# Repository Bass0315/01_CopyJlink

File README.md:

# Jflash auto dowmload
#### 介绍
> 该项目是 Windows/Linux 下Jflash的自动烧录脚本。

#### 支持
Linux：
> sudo apt-get install libudev-dev
> sudo apt-get install gcc./
> sudo apt-get install build-essential
> Install libusb (https://blog.csdn.net/p1279030826/article/details/102891704)
> ~$ sudo cp 99-jlink.rules /etc/udev/rules.d 

#### 使用
Linux：
> Program.sh  xxx.bin/hex

Windows:

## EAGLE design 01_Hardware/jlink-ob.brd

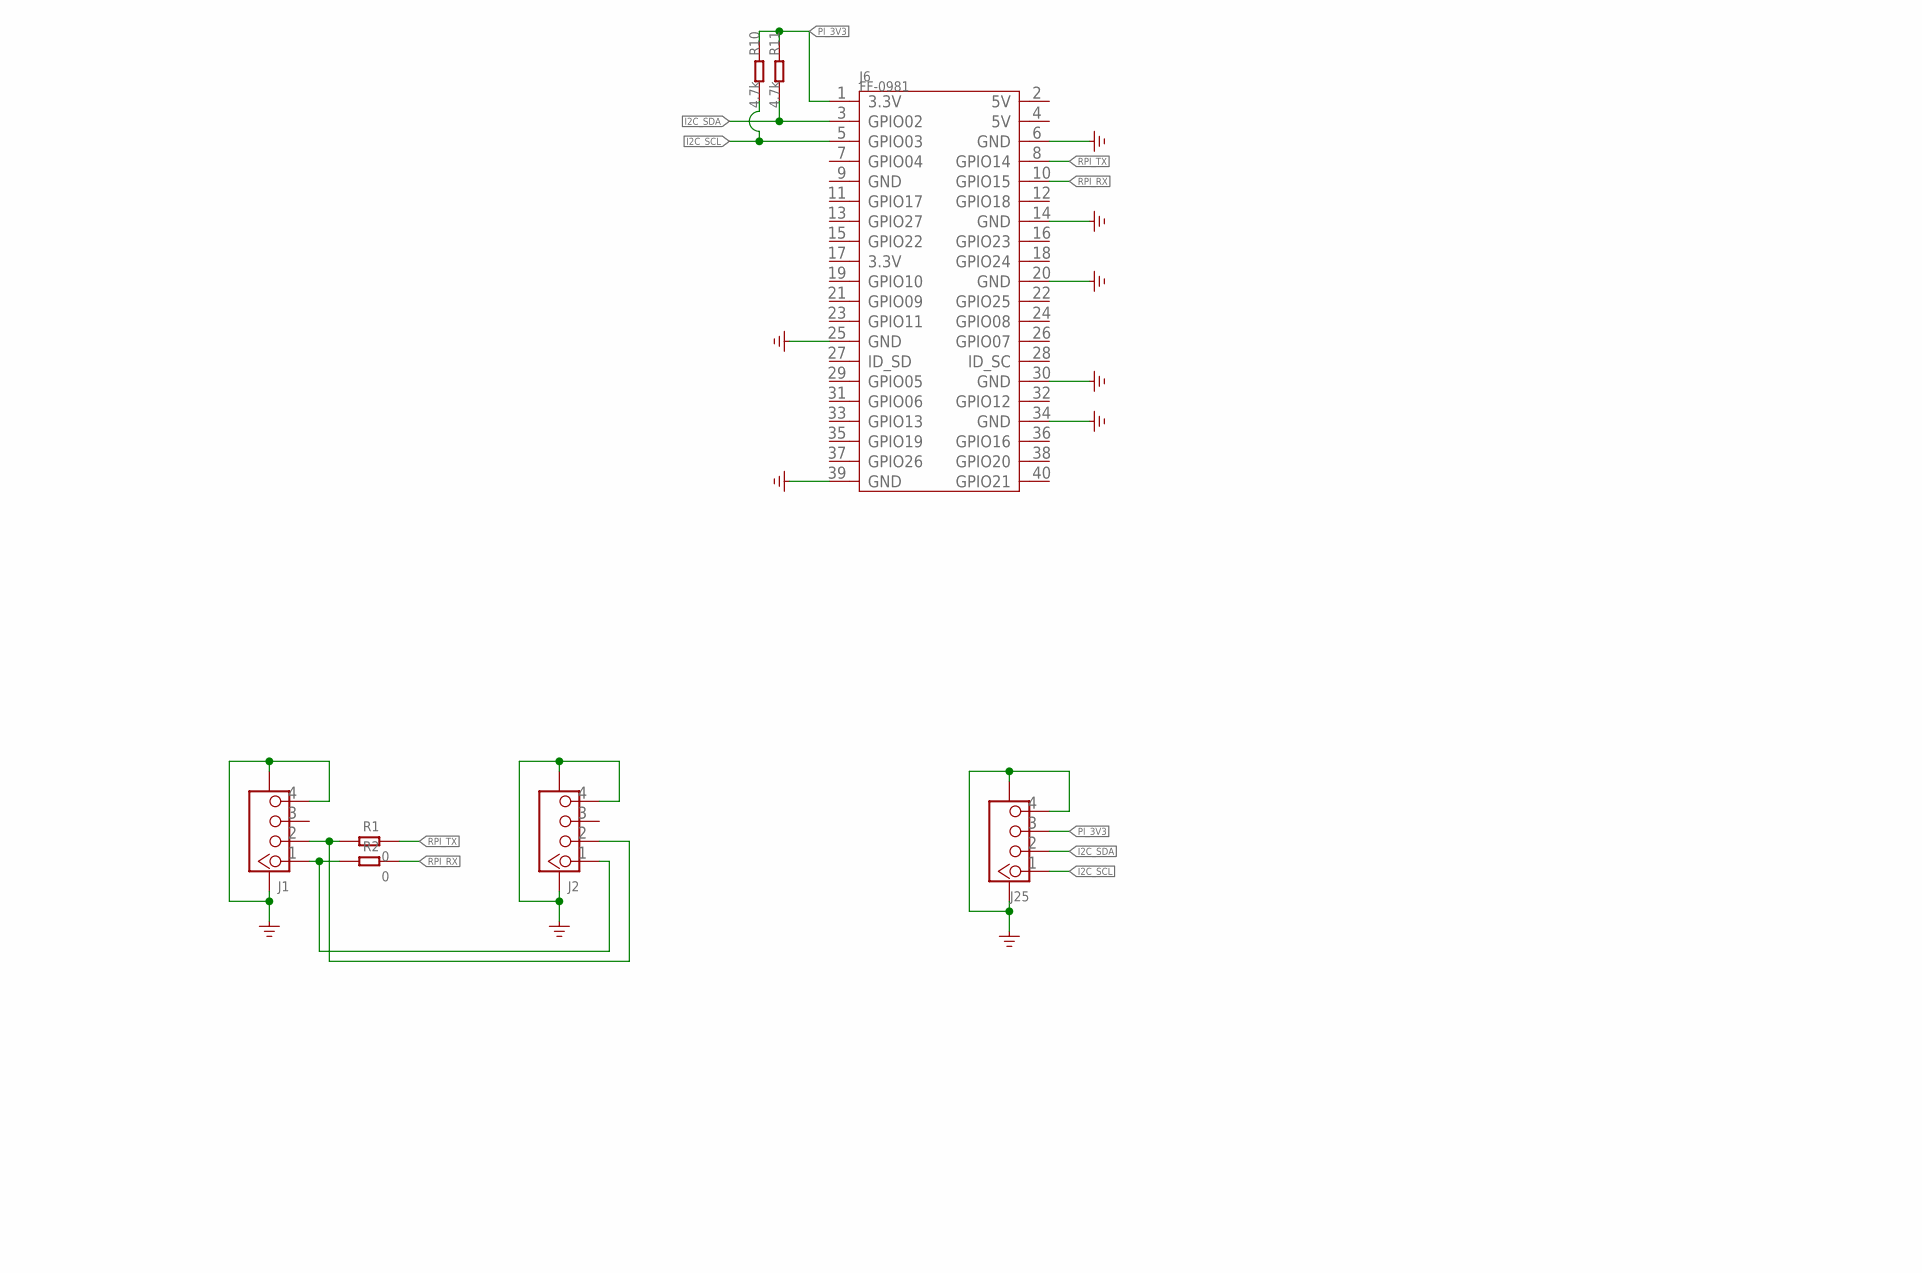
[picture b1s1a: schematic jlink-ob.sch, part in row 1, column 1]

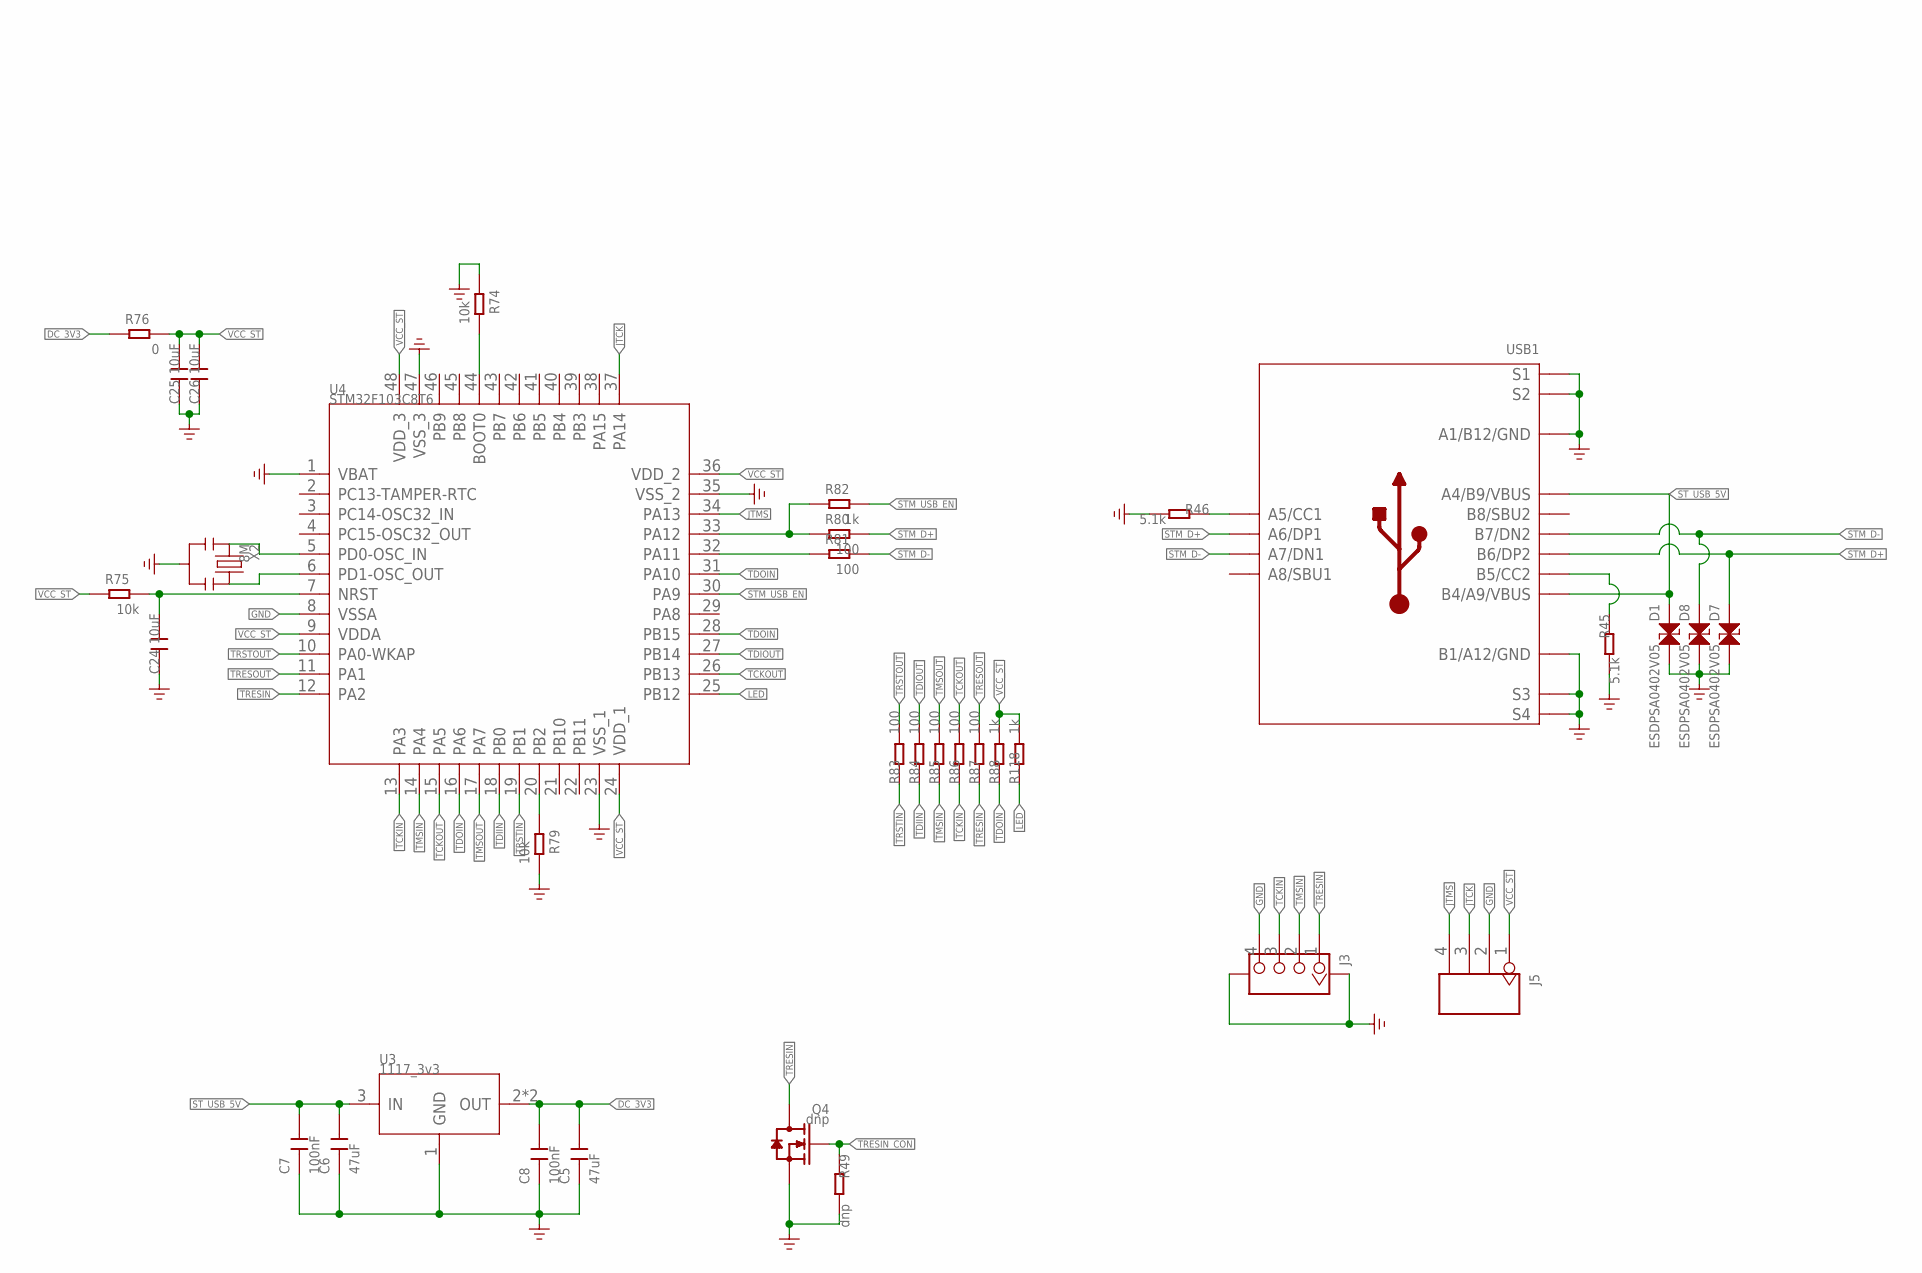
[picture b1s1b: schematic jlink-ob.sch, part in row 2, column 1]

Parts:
C5, C6: 47uF; C1206
C7, C8: 100nF; C0603
C24, C25, C26: 10uF; C0603
D1, D7, D8: ESDPSA0402V05; ESD-0402
J1, J2, J3, J25: GROVE-CONNECTOR-SMD-320110032; HW4-SMD-2.0-90D
J5: HEADER-4P-65/35MIL; H4-2.54-65/35MIL
J6: FF-0981; H2X20-2.54
Q4: dnp; SOT-23
R1, R2, R76: 0; R0603
R10, R11: 4.7k; R0603
R45, R46: 5.1k; R0603
R49: dnp; R0603
R74, R75, R79: 10k; R0603
R80, R81, R83, R84, R85, R86, R87: 100; R0603
R82, R88, R118: 1k; R0603
U3: 1117_3v3; SOT-223
U4: STM32F103C8T6; LQFP48
USB1: USB2.0-TYPE-C-320010698; USB2.0-TYPE-C
X2: 8M; RESONATOR3-SMD-3.6X1.3X0.8MM

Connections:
DC_3V3: C5.2, C8.2, R76.2, U3.2 (OUT), U3.TER (OUT)
GND: C5.1, C6.1, C7.1, C8.1, C24.1, C25.1, C26.1, D1.2, D7.2, D8.2, J1.4, J1.SS1, J1.SS2, J2.4, J2.SS1, J2.SS2, J3.4, J3.SS1, J3.SS2, J5.2, J6.6 (GND), J6.14 (GND), J6.20 (GND), J6.25 (GND), J6.30 (GND), J6.34 (GND), J6.39 (GND), J25.4, J25.SS1, J25.SS2, Q4.2 (S), R45.2, R46.2, R49.2, R74.2, R79.1, U3.1 (GND), U4.1 (VBAT), U4.8 (VSSA), U4.23 (VSS_1), U4.35 (VSS_2), U4.47 (VSS_3), USB1.A1_B12 (A1/B12/GND), USB1.B1_A12 (B1/A12/GND), USB1.S1, USB1.S2, USB1.S3, USB1.S4, USB1.S5 (S1), USB1.S6 (S2), X2.2
I2C_SCL: J6.5 (GPIO03), J25.1, R10.1
I2C_SDA: J6.3 (GPIO02), J25.2, R11.1
JTCK: J5.3, U4.37 (PA14)
JTMS: J5.4, U4.34 (PA13)
LED: R118.1, U4.25 (PB12)
unnamed: J1.1, J2.1, R2.2
unnamed: J1.2, J2.2, R1.2
unnamed: R46.1, USB1.A5 (A5/CC1)
unnamed: R45.1, USB1.B5 (B5/CC2)
unnamed: R80.2, R82.2, U4.33 (PA12)
unnamed: R81.2, U4.32 (PA11)
unnamed: U4.5 (PD0-OSC_IN), X2.1
unnamed: U4.6 (PD1-OSC_OUT), X2.3
unnamed: R79.2, U4.20 (PB2)
unnamed: R74.1, U4.44 (BOOT0)
unnamed: C24.2, R75.1, U4.7 (NRST)
PI_3V3: J6.1 (3.3V), J25.3, R10.2, R11.2
RPI_RX: J6.10 (GPIO15), R2.1
RPI_TX: J6.8 (GPIO14), R1.1
STM_D+: D7.1, R80.1, USB1.A6 (A6/DP1), USB1.B6 (B6/DP2)
STM_D-: D8.1, R81.1, USB1.A7 (A7/DN1), USB1.B7 (B7/DN2)
STM_USB_EN: R82.1, U4.30 (PA9)
ST_USB_5V: C6.2, C7.2, D1.1, U3.3 (IN), USB1.A4_B9 (A4/B9/VBUS), USB1.B4_A9 (B4/A9/VBUS)
TCKIN: J3.3, R86.1, U4.13 (PA3)
TCKOUT: R86.2, U4.15 (PA5), U4.26 (PB13)
TDIIN: R84.1, U4.18 (PB0)
TDIOUT: R84.2, U4.27 (PB14)
TDOIN: R88.1, U4.16 (PA6), U4.28 (PB15), U4.31 (PA10)
TMSIN: J3.2, R85.1, U4.14 (PA4)
TMSOUT: R85.2, U4.17 (PA7)
TRESIN: J3.1, Q4.3 (D), R87.1, U4.12 (PA2)
TRESIN_CON: Q4.1 (G), R49.1
TRESOUT: R87.2, U4.11 (PA1)
TRSTIN: R83.1, U4.19 (PB1)
TRSTOUT: R83.2, U4.10 (PA0-WKAP)
VCC_ST: C25.2, C26.2, J5.1, R75.2, R76.1, R88.2, R118.2, U4.9 (VDDA), U4.24 (VDD_1), U4.36 (VDD_2), U4.48 (VDD_3)

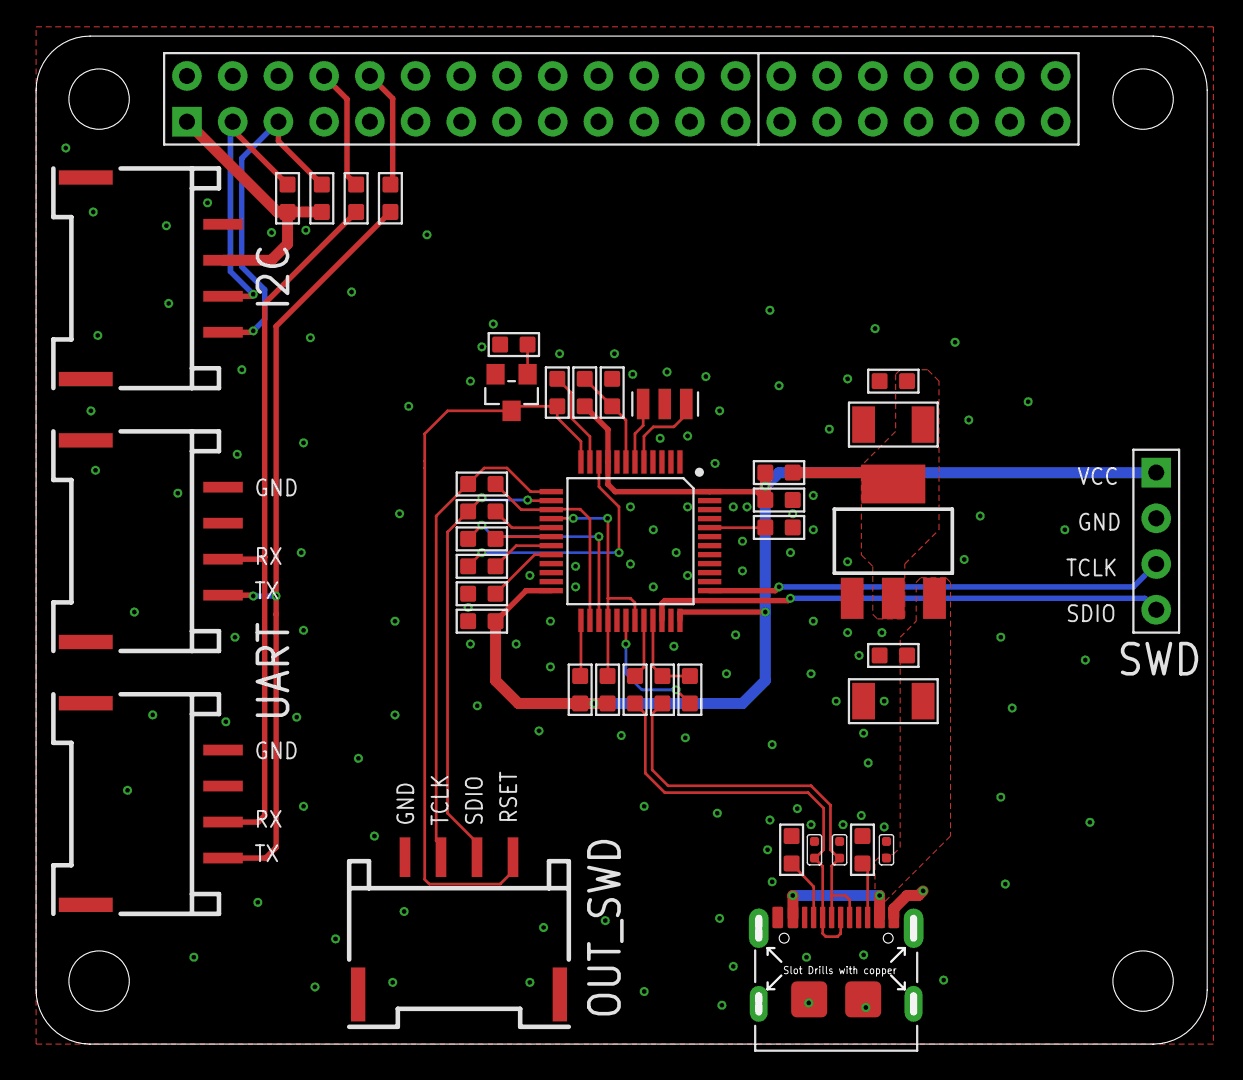
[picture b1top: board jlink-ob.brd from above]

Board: 2 copper layers, 64.7 x 55.6 mm, 42 parts (1 on the bottom side), 38 nets.

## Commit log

2022-06-24 第一次上传
2022-06-26 Edit linux auto download program.
2022-06-26 edit README
